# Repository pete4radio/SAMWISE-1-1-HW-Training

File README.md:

# SAMWISE-1-1-HW-Training
PCBs fabbed in May 2024 for SAMWISE

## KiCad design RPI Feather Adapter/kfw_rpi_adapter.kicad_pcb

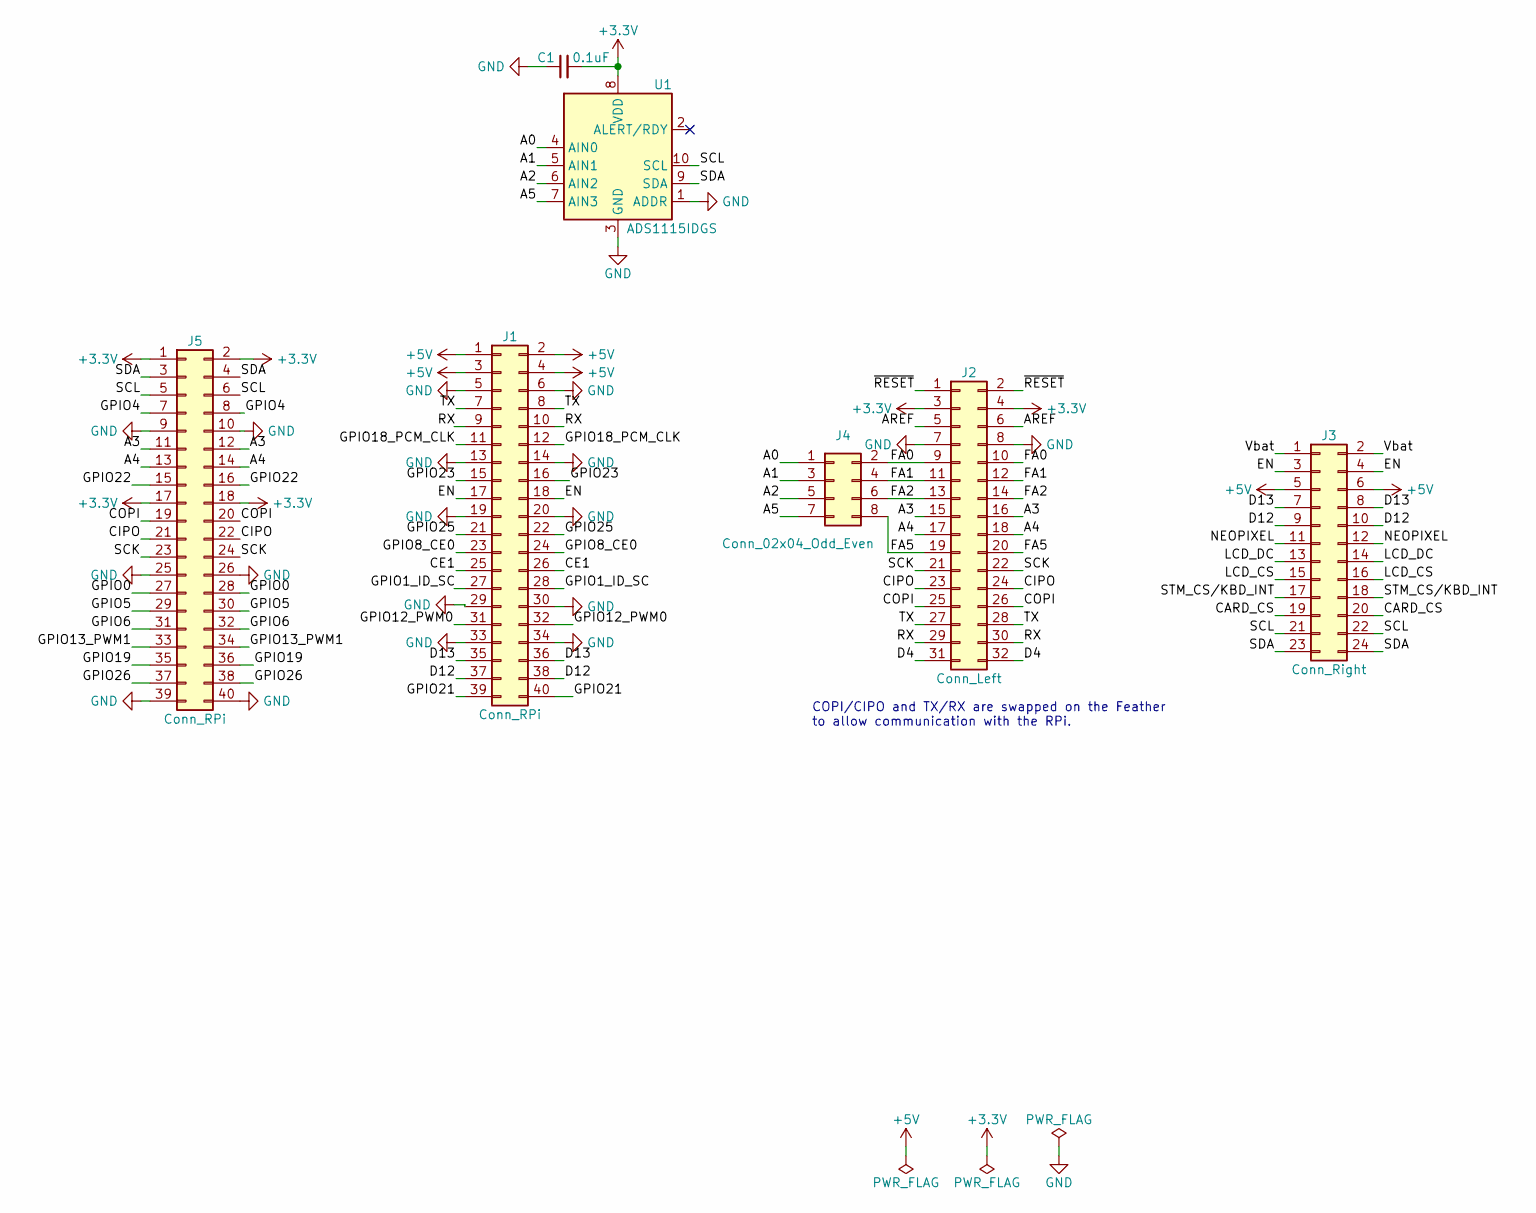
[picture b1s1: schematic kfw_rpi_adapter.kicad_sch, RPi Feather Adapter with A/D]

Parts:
C1: 0.1uF; C_0603_1608Metric
J1, J5: Conn_RPi; PinHeader_2x20_P2.54mm_Vertical
J2: Conn_Left; PinHeader_2x16_P2.54mm_Vertical
J3: Conn_Right; PinHeader_2x12_P2.54mm_Vertical
J4: Conn_02x04_Odd_Even; PinHeader_2x04_P2.54mm_Vertical
U1: ADS1115IDGS; TSSOP-10_3x3mm_P0.5mm

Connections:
+3V3: C1.2, J2.3, J2.4, J5.1, J5.2, J5.17, J5.18, U1.8 (VDD)
+5V: J1.1, J1.2, J1.3, J1.4, J3.5, J3.6
/A0: J4.1, U1.4 (AIN0)
/A1: J4.3, U1.5 (AIN1)
/A2: J4.5, U1.6 (AIN2)
/A3: J2.15, J2.16, J5.11, J5.12
/A4: J2.17, J2.18, J5.13, J5.14
/A5: J4.7, U1.7 (AIN3)
/AREF: J2.5, J2.6
/CARD_CS: J3.19, J3.20
/CE1: J1.25, J1.26; also elsewhere on the board
/CIPO: J2.23, J2.24, J5.21, J5.22
/COPI: J2.25, J2.26, J5.19, J5.20
/D4: J2.31, J2.32
/D12: J1.37, J1.38, J3.9, J3.10
/D13: J1.35, J1.36, J3.7, J3.8
/EN: J1.17, J1.18, J3.3, J3.4
/FA0: J2.9, J2.10, J4.2
/FA1: J2.11, J2.12, J4.4
/FA2: J2.13, J2.14, J4.6
/FA5: J2.19, J2.20, J4.8
/GPIO0: J5.27, J5.28
/GPIO1_ID_SC: J1.27, J1.28
/GPIO4: J5.7, J5.8; also elsewhere on the board
/GPIO5: J5.29, J5.30
/GPIO6: J5.31, J5.32
/GPIO8_CE0: J1.23, J1.24
/GPIO12_PWM0: J1.31, J1.32
/GPIO13_PWM1: J5.33, J5.34
/GPIO18_PCM_CLK: J1.11, J1.12
/GPIO19: J5.35, J5.36
/GPIO21: J1.39, J1.40
/GPIO22: J5.15, J5.16
/GPIO23: J1.15, J1.16
/GPIO25: J1.21, J1.22
/GPIO26: J5.37, J5.38
/LCD_CS: J3.15, J3.16
/LCD_DC: J3.13, J3.14
/NEOPIXEL: J3.11, J3.12
/RX: J1.9, J1.10, J2.29, J2.30
/SCK: J2.21, J2.22, J5.23, J5.24
/SCL: J3.21, J3.22, J5.5, J5.6, U1.10 (SCL)
/SDA: J3.23, J3.24, J5.3, J5.4, U1.9 (SDA)
/STM_CS/KBD_INT: J3.17, J3.18; also elsewhere on the board
/TX: J1.7, J1.8, J2.27, J2.28
/Vbat: J3.1, J3.2
/~RESET: J2.1, J2.2
GND: C1.1, J1.5, J1.6, J1.13, J1.14, J1.19, J1.20, J1.29, J1.30, J1.33, J1.34, J2.7, J2.8, J5.9, J5.10, J5.25, J5.26, J5.39, J5.40, U1.1 (ADDR), U1.3 (GND)

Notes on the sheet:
COPI/CIPO and TX/RX are swapped on the Feather to allow communication with the RPi.

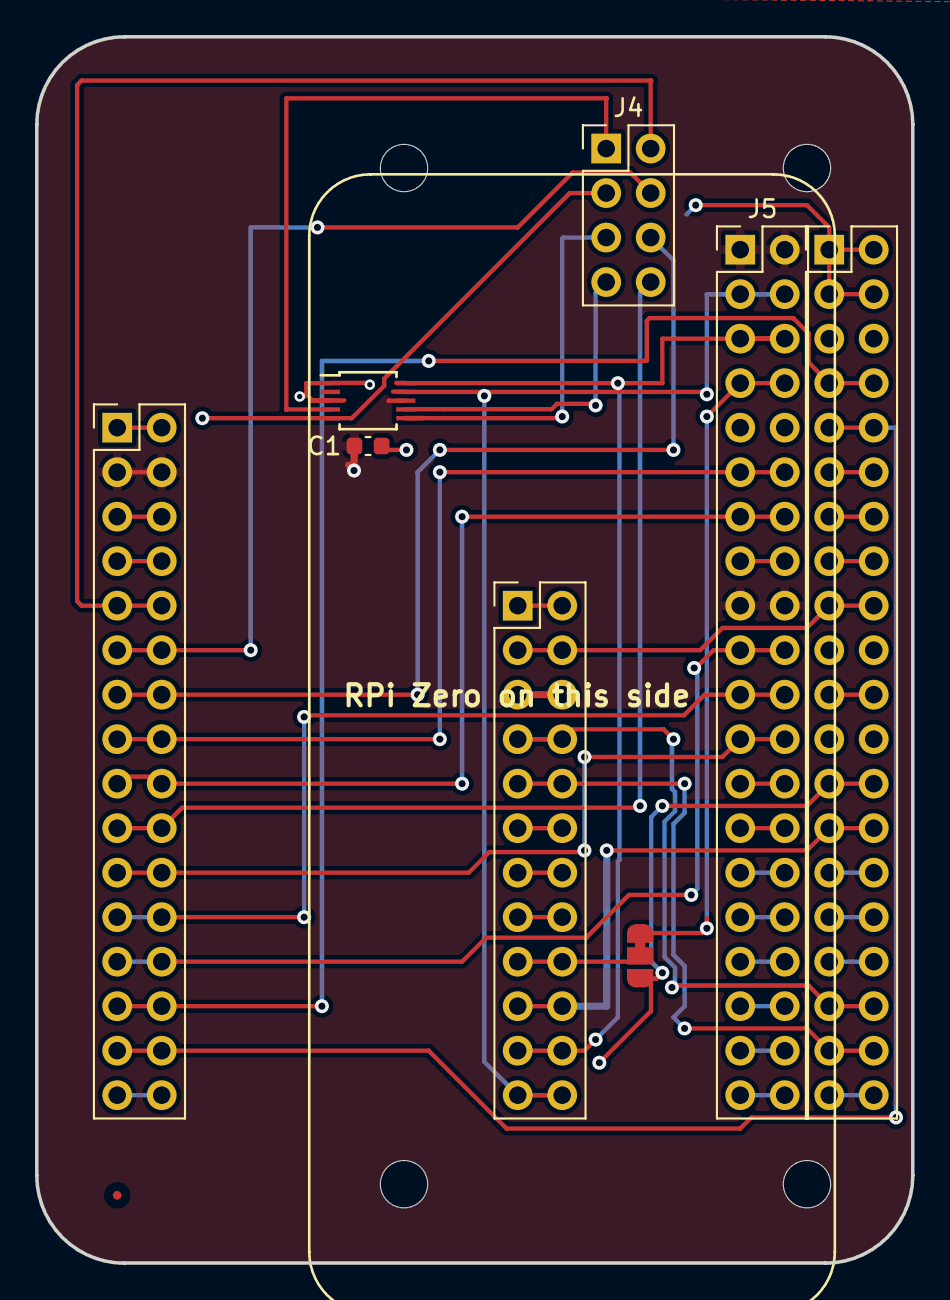
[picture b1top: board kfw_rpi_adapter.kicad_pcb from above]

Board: 2 copper layers, 50.0 x 70.0 mm, 8 parts (0 on the bottom side), 48 nets.

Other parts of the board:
JP1: SJ_STM_KBD; SolderJumper-3_P1.3mm_Bridged12_RoundedPad1.0x1.5mm_NumberL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

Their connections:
/CE1: JP1.3 (B); also elsewhere on the board
/GPIO4: JP1.1 (A); also elsewhere on the board
/STM_CS/KBD_INT: JP1.2 (C); also elsewhere on the board

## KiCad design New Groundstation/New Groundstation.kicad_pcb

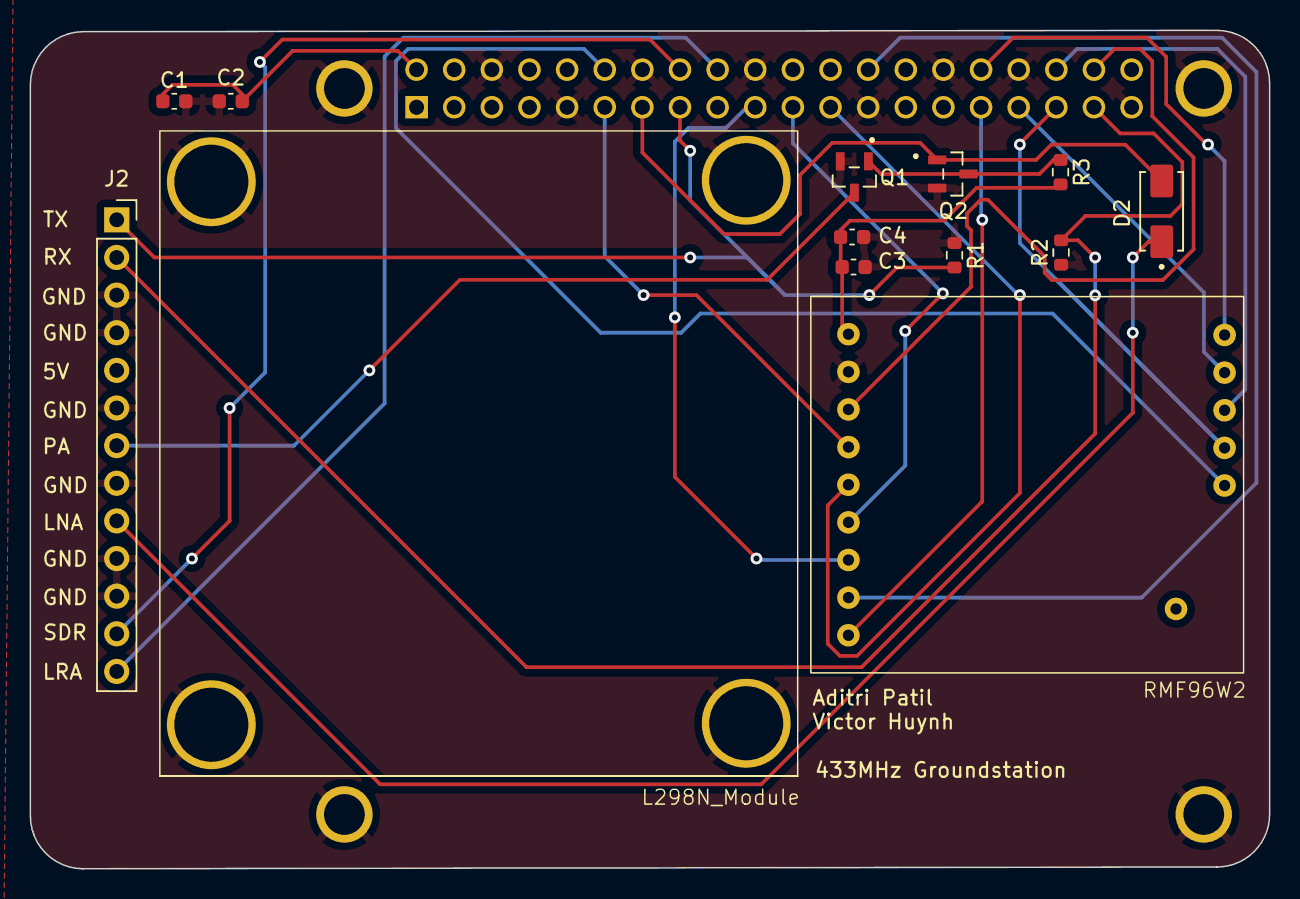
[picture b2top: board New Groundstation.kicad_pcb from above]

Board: 4 copper layers, 83.6 x 56.6 mm, 14 parts (0 on the bottom side), 22 nets.

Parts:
C1, C3: 10uF; C_0603_1608Metric
C2, C4: 0.1uF; C_0603_1608Metric
D2: M7; DIOM505270X240
J2: Conn_01x13_Pin; PinSocket_1x13_P2.54mm_Vertical
L298N_Module: L298N_Module; H-bridge module
Q1, Q2: 2N7002; SOT95P240X111-3N
R1, R2: 10k; R_0603_1608Metric
R3: 100k; R_0603_1608Metric
RMF96W2: RFM96W1
U2: RASPBERRY_PI_4B_4GB; MODULE_RASPBERRY_PI_4B_4GB

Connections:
+5V: C1.1, C2.1, C3.1, C4.1, J2.5, R3.2, RMF96W2.1 (Vin), U2.2 (5V), U2.4 (5V)
/CS: RMF96W2.8 (CS), U2.26 (GPIO7/~SPI_CE1)
/DIO0: RMF96W2.4 (DIO0), U2.11 (GPIO17/GPIO_GEN0)
/DIO1: RMF96W2.10 (DIO1), U2.32 (GPIO12)
/DIO2: RMF96W2.11 (DIO2), U2.33 (GPIO13)
/DIO3: RMF96W2.12 (DIO3), U2.36 (GPIO16)
/DIO4: RMF96W2.13 (DIO4), U2.35 (GPIO19)
/DIO5: RMF96W2.14 (DIO5), U2.12 (GPIO18/GPIO_GEN1)
/MISO: RMF96W2.6 (MISO), U2.21 (GPIO9/SPI_MISO)
/MOSI: RMF96W2.7 (MOSI), U2.19 (GPIO10/SPI_MOSI)
/PTT_OUT: D2.A, Q2.1, U2.13 (GPIO27/GPIO_GEN2)
/RST: RMF96W2.9 (RST), U2.31 (GPIO6)
/SCK: RMF96W2.5 (SCK), U2.23 (GPIO11/SPI_SCLK)
/enable: RMF96W2.3 (EN), U2.38 (GPIO20)
GND: C1.2, C2.2, C3.2, C4.2, J2.3, J2.4, J2.6, J2.8, J2.10, J2.11, L298N_Module.4 (GND), Q1.2, Q2.2, R1.1, R2.1, RMF96W2.2 (GND), U2.6 (GND), U2.9 (GND), U2.14 (GND), U2.20 (GND), U2.25 (GND), U2.30 (GND), U2.34 (GND), U2.39 (GND), U2.S1 (SHIELD), U2.S2 (SHIELD), U2.S3 (SHIELD), U2.S4 (SHIELD)
LNA_PTT: D2.C, J2.9
LORA_CTRL: J2.13, U2.18 (GPIO24/GPIO_GEN5)
unnamed: Q1.1, Q2.3, R3.1
PA_PTT: J2.7, Q1.3
RX_CTRL: J2.2, R2.2, U2.37 (GPIO26)
SDR_CTRL: J2.12, U2.16 (GPIO23/GPIO_GEN4)
TX_CTRL: J2.1, R1.2, U2.15 (GPIO22/GPIO_GEN3)

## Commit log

2024-05-09 Initial load after orders placed
2024-05-15 Updated pycubed
    pycubed changes as a result of several design reviews were sent off for fab 14-May. To quote from Slack the Pycubed has been ordered!! :tada::tada::party-parrot: :party_cat: the Pycubed is the shire 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
